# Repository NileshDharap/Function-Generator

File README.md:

# Function-Generator
Function Generator Circuit using AD9833 module and Stm32 controller

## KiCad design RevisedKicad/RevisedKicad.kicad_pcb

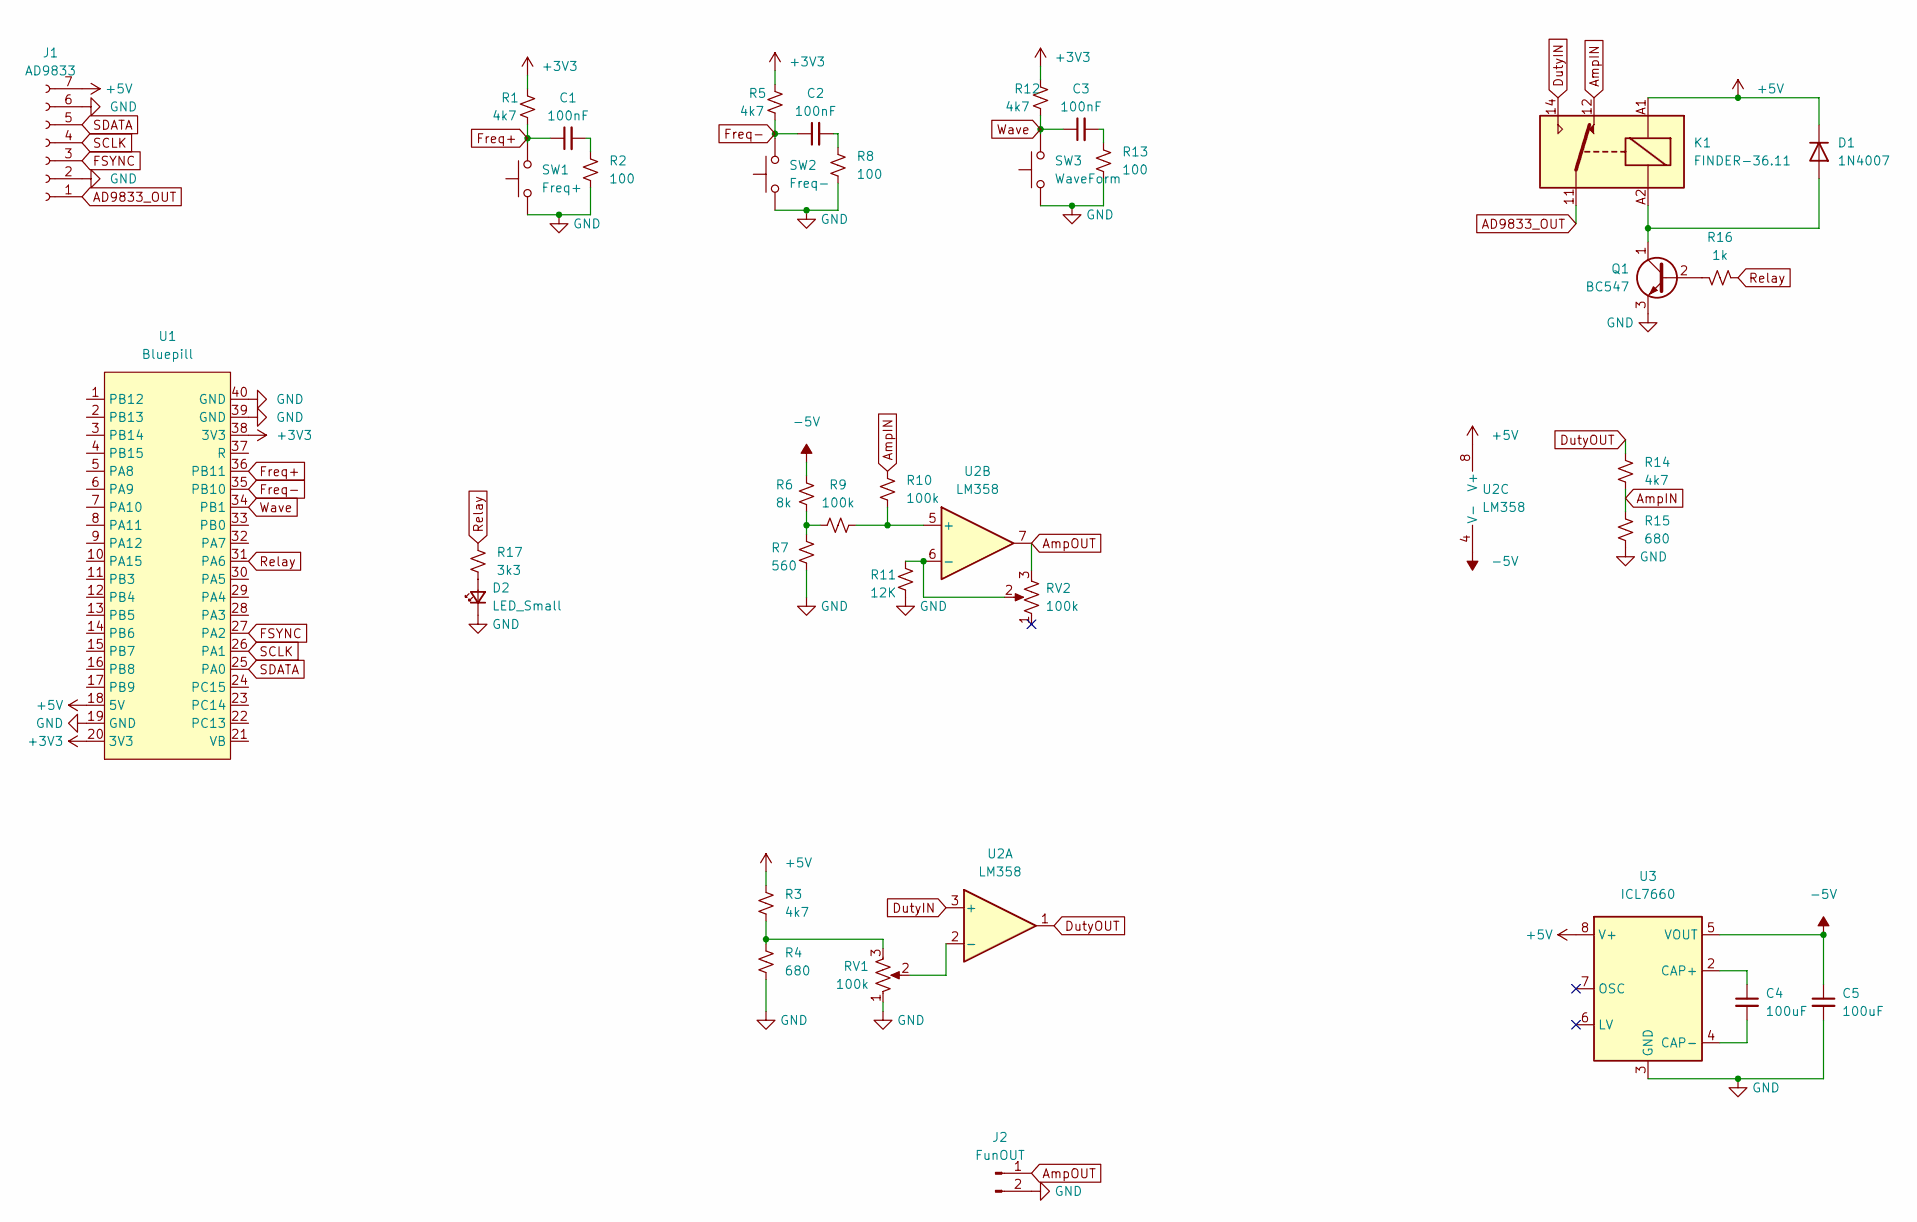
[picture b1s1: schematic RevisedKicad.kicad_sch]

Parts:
C1, C2, C3: 100nF; CP_Radial_D10.0mm_P3.80mm
C4, C5: 100uF; CP_Radial_D12.5mm_P5.00mm
D1: 1N4007; D_DO-41_SOD81_P10.16mm_Horizontal
D2: LED_Small; LED_D3.0mm
J1: AD9833; PinSocket_1x07_P2.54mm_Vertical
J2: FunOUT; PinHeader_1x02_P2.54mm_Vertical
K1: FINDER-36.11; Relay_SPDT_Finder_36.11
Q1: BC547; TO-92_Inline
R1, R3, R5, R12, R14: 4k7; R_Axial_DIN0414_L11.9mm_D4.5mm_P15.24mm_Horizontal
R2, R8, R13: 100; R_Axial_DIN0414_L11.9mm_D4.5mm_P15.24mm_Horizontal
R4, R15: 680; R_Axial_DIN0414_L11.9mm_D4.5mm_P15.24mm_Horizontal
R6: 8k; R_Axial_DIN0414_L11.9mm_D4.5mm_P15.24mm_Horizontal
R7: 560; R_Axial_DIN0414_L11.9mm_D4.5mm_P15.24mm_Horizontal
R9, R10: 100k; R_Axial_DIN0414_L11.9mm_D4.5mm_P15.24mm_Horizontal
R11: 12K; R_Axial_DIN0414_L11.9mm_D4.5mm_P15.24mm_Horizontal
R16: 1k; R_Axial_DIN0414_L11.9mm_D4.5mm_P15.24mm_Horizontal
R17: 3k3; R_Axial_DIN0414_L11.9mm_D4.5mm_P15.24mm_Horizontal
RV1, RV2: 100k; Potentiometer_Alps_RK09Y11_Single_Horizontal
SW1: Freq+; SW_PUSH_6mm_H7.3mm
SW2: Freq-; SW_PUSH_6mm_H7.3mm
SW3: WaveForm; SW_PUSH_6mm_H7.3mm
U1: Bluepill
U2: LM358; DIP-8_W7.62mm_Socket_LongPads
U3: ICL7660; DIP-8_W7.62mm_Socket_LongPads

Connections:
+3V3: R1.1, R5.1, R12.1, U1.20 (3V3), U1.38 (3V3)
+5V: D1.1 (K), J1.7, K1.A1, R3.1, U1.18 (5V), U2.8 (V+), U3.8 (V+)
-5V: C5.1, R6.1, U2.4 (V-), U3.5 (VOUT)
AD9833_OUT: J1.1, K1.11
AmpIN: K1.12, R10.1, R14.2, R15.1
AmpOUT: J2.1, RV2.3, U2.7
DutyIN: K1.14, U2.3 (+)
DutyOUT: R14.1, U2.1
FSYNC: J1.3, U1.27 (PA2)
Freq+: C1.1, R1.2, SW1.2, U1.36 (PB11)
Freq-: C2.1, R5.2, SW2.2, U1.35 (PB10)
GND: C5.2, D2.1 (K), J1.2, J1.6, J2.2, Q1.3 (E), R2.2, R4.2, R7.2, R8.2, R11.2, R13.2, R15.2, RV1.1, SW1.1, SW2.1, SW3.1, U1.19 (GND), U1.39 (GND), U1.40 (GND), U3.3 (GND)
unnamed: C1.2, R2.1
unnamed: C2.2, R8.1
unnamed: C3.2, R13.1
unnamed: C4.1, U3.2 (CAP+)
unnamed: C4.2, U3.4 (CAP-)
unnamed: D1.2 (A), K1.A2, Q1.1 (C)
unnamed: D2.2 (A), R17.2
unnamed: Q1.2 (B), R16.2
unnamed: R3.2, R4.1, RV1.3
unnamed: R6.2, R7.1, R9.2
unnamed: R9.1, R10.2, U2.5 (+)
unnamed: R11.1, RV2.2, U2.6 (-)
unnamed: RV1.2, U2.2 (-)
Relay: R16.1, R17.1, U1.31 (PA6)
SCLK: J1.4, U1.26 (PA1)
SDATA: J1.5, U1.25 (PA0)
Wave: C3.1, R12.2, SW3.2, U1.34 (PB1)

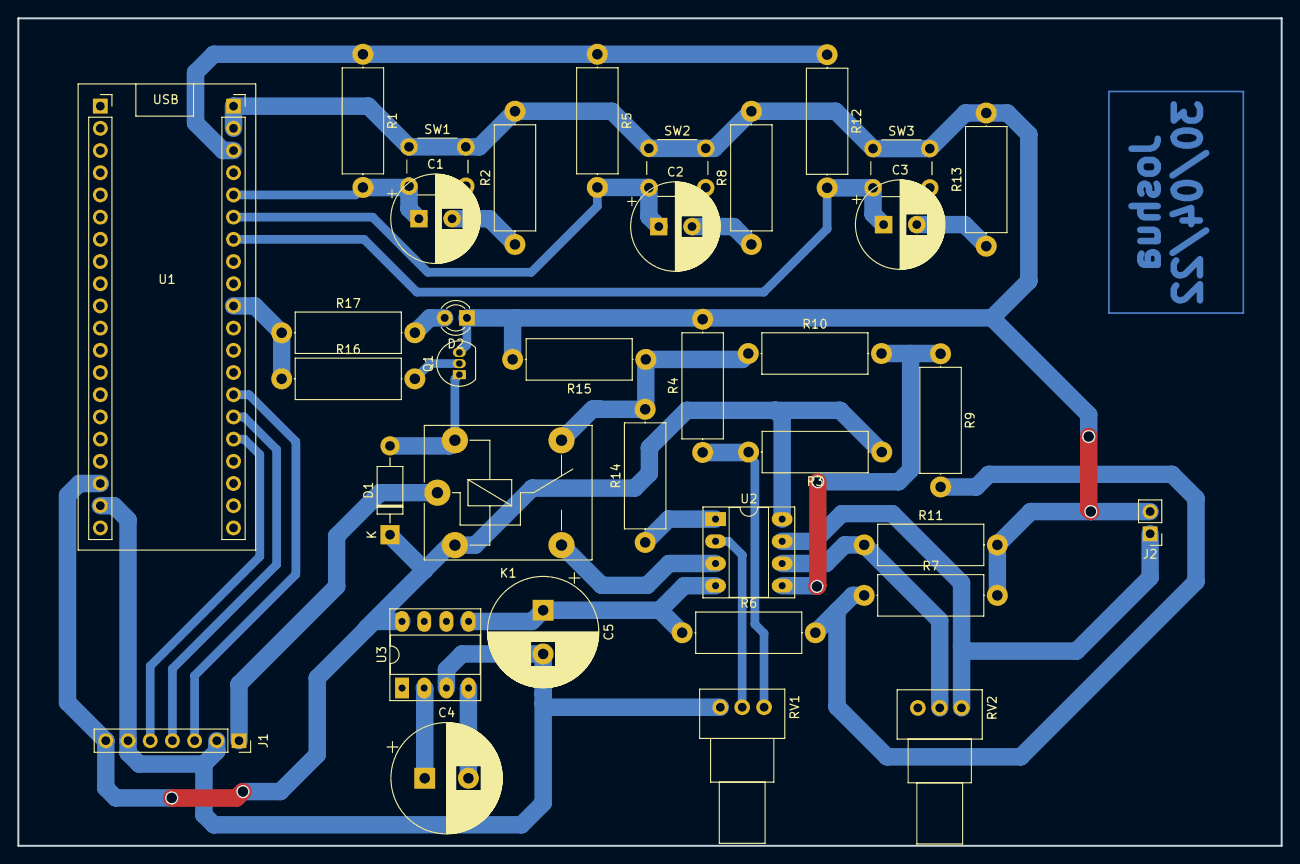
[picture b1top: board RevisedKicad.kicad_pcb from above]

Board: 2 copper layers, 144.5 x 94.7 mm, 36 parts (0 on the bottom side), 29 nets.

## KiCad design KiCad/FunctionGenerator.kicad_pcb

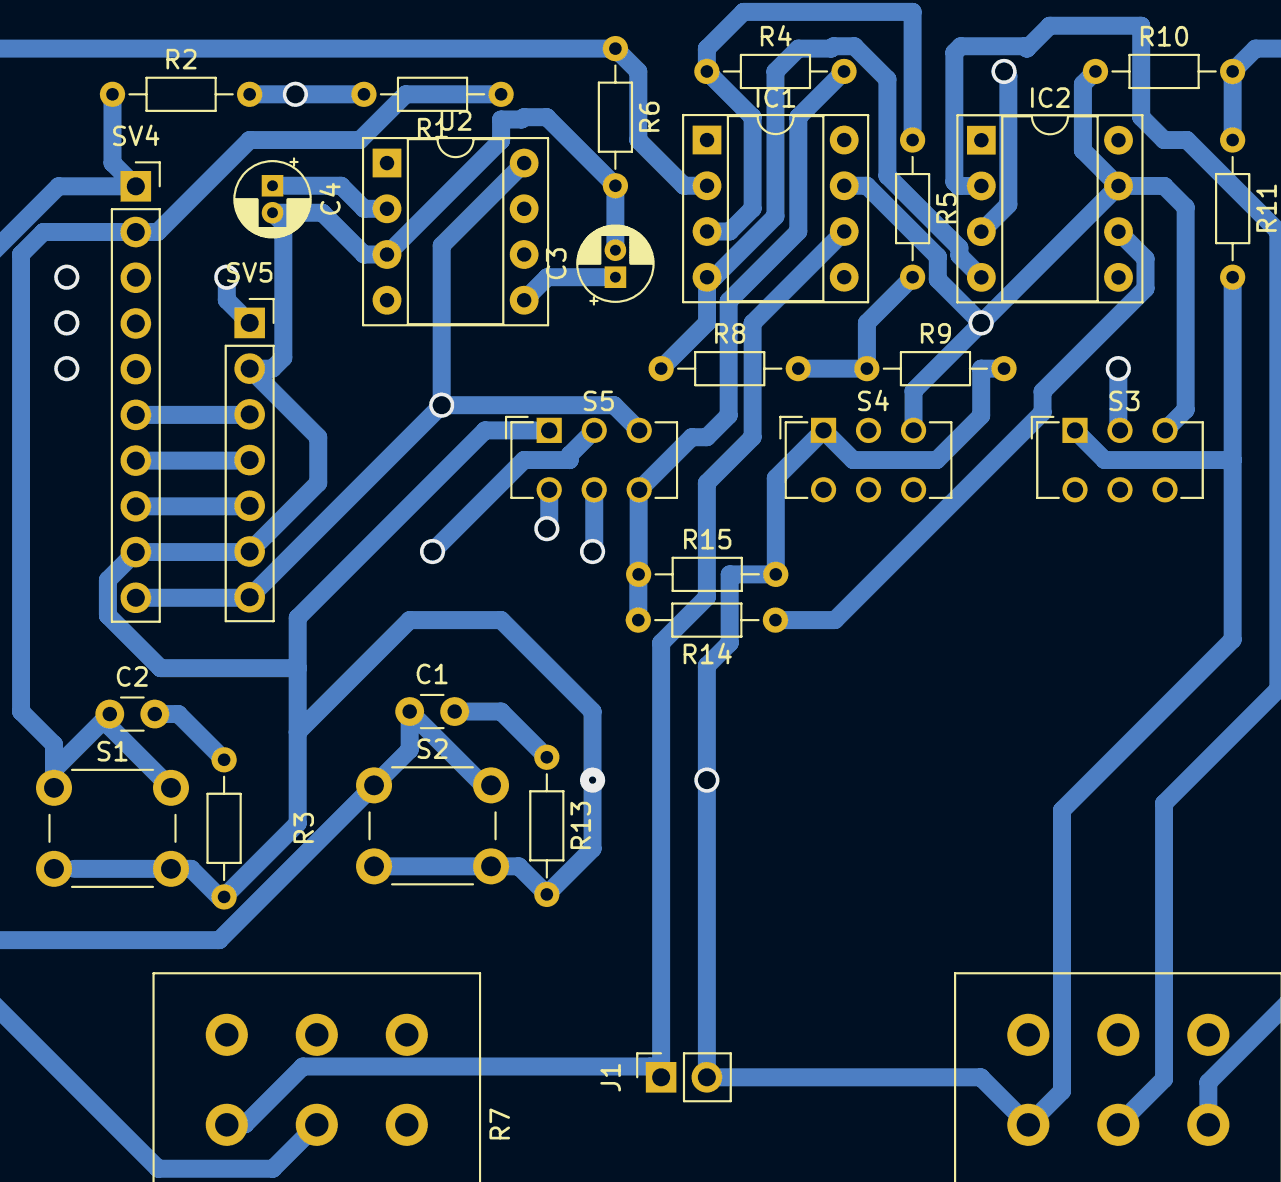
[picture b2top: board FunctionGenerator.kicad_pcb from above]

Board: 2 copper layers, 30 parts (0 on the bottom side), 25 nets.

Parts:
C1, C2: 100nF; C_Disc_D3.0mm_W1.6mm_P2.50mm
C3, C4: 100uF; CP_Radial_D4.0mm_P1.50mm
IC1, IC2: 741P; DIP-8_W7.62mm_Socket
J1: Conn_01x02_Female; PinSocket_1x02_P2.54mm_Vertical
R1, R2, R10, R14: 4.7k; R_Axial_DIN0204_L3.6mm_D1.6mm_P7.62mm_Horizontal
R3, R13: 100; R_Axial_DIN0204_L3.6mm_D1.6mm_P7.62mm_Horizontal
R4, R5: 100k; R_Axial_DIN0204_L3.6mm_D1.6mm_P7.62mm_Horizontal
R6: 12k; R_Axial_DIN0204_L3.6mm_D1.6mm_P7.62mm_Horizontal
R7: 3RP/1610N; Potentiometer_Alps_RK163_Dual_Horizontal
R8: 8k; R_Axial_DIN0204_L3.6mm_D1.6mm_P7.62mm_Horizontal
R9: 560; R_Axial_DIN0204_L3.6mm_D1.6mm_P7.62mm_Horizontal
R11, R15: 680; R_Axial_DIN0204_L3.6mm_D1.6mm_P7.62mm_Horizontal
R12: 100k; Potentiometer_Alps_RK163_Dual_Horizontal
S1, S2: 10-XX; SW_PUSH_6mm_H4.3mm
S3, S4, S5: PVA2; SW_CuK_JS202011CQN_DPDT_Straight
SV4: FE10-1; PinSocket_1x10_P2.54mm_Vertical
SV5: FE07-1; PinSocket_1x07_P2.54mm_Vertical
U2: ICL7660SIPAZ; DIP-8_W7.62mm_Socket

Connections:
+5V: IC1.7 (V+), IC2.7 (V+), R1.2, R2.2, R10.1, S3.3 (O), S4.3 (O), S5.3 (O), SV4.10, SV5.7, U2.8 (V+)
-5V: IC1.4 (V-), IC2.4 (V-), R8.1
/0.65V: R10.2, R11.1, R12.3 (E)
/FMINUS: C1.1, R2.1, S2.1 (S), SV4.1
/FPLUS: C2.1, R1.1, S1.1 (S), SV4.2
/FSYNC: SV4.6, SV5.3
/OUT: S5.5, SV5.1
/SCLK: SV4.7, SV5.4
/SDATA: SV4.8, SV5.5
/SIN: S3.2, SV4.5
/SQR: S5.2, SV4.4
/TRI: S4.2, SV4.3
/VIN_AMP: R4.2, R14.2, R15.1, S5.6 (O)
/VIN_DUT: IC2.3 (+IN), S5.4 (S)
/VOUT_AMP: IC1.6 (OUT), J1.1, R7.1 (A)
/VOUT_DUT: IC2.6 (OUT), R14.1
GND: C3.2, C4.2, J1.2, R3.2, R6.2, R9.2, R11.2, R12.1 (A), R13.2, R15.2, S1.2 (S1), S2.2 (S1), S3.1 (S), S4.1 (S), S5.1 (S), SV4.9, SV5.2, SV5.6, U2.3 (GND)
unnamed: C1.2, R13.1
unnamed: C2.2, R3.1
unnamed: C4.1, U2.2 (CAP+)
unnamed: C3.1, U2.5 (VOUT)
unnamed: IC1.2 (-IN), R6.1, R7.2 (S)
unnamed: IC1.3 (+IN), R4.1, R5.1
unnamed: IC2.2 (-IN), R12.2 (S)
unnamed: R5.2, R8.2, R9.1

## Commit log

2022-04-12 Create Switches
2022-04-12 Added files
2022-04-29 added schematic
2022-04-30 Revised........
